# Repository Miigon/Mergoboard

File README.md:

# Mergoboard

38-key split ergonomic keyboard made with #ergogen.
## Note
This project is heavily based on [samoklava](https://github.com/soundmonster/samoklava) and uses much of the same footprints.
All the additional footprints or modified footprints are in the `footprints` folder.

## Screenshot
### rev0 (2022-05-02)

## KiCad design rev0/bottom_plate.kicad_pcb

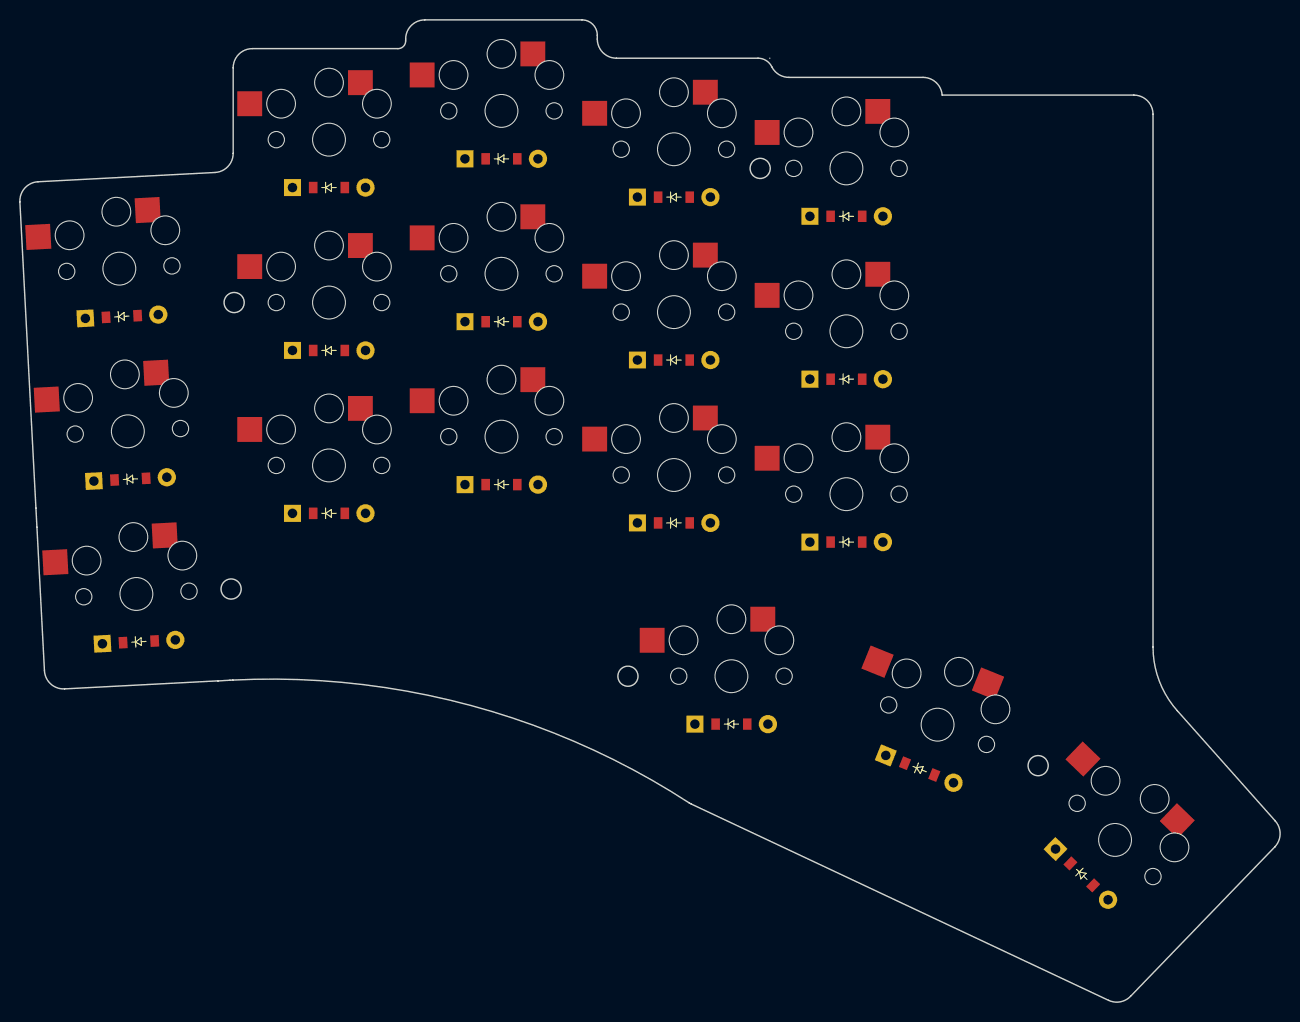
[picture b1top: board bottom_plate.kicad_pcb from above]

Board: 2 copper layers, 131.5 x 102.5 mm, 36 parts (0 on the bottom side), 27 nets, no tracks yet.

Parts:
D1, D2, D3, D4, D5, D6, D7, D8, D9, D10, D11, D12, D13, D14, D15, D16, D17, D18: ComboDiode
S1, S2, S3, S4, S5, S6, S7, S8, S9, S10, S11, S12, S13, S14, S15, S16, S17, S18: PG1350

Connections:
P4: D3.1, D3.2, D6.1, D6.2, D9.1, D9.2, D12.1, D12.2, D15.1, D15.2
P5: D2.1, D2.2, D5.1, D5.2, D8.1, D8.2, D11.1, D11.2, D14.1, D14.2
P6: D1.1, D1.2, D4.1, D4.2, D7.1, D7.2, D10.1, D10.2, D13.1, D13.2
P7: D16.1, D16.2, D17.1, D17.2, D18.1, D18.2
P14: S13.2, S14.2, S15.2, S18.2
P15: S10.2, S11.2, S12.2, S17.2
P18: S7.2, S8.2, S9.2, S16.2
P19: S4.2, S5.2, S6.2
P20: S1.2, S2.2, S3.2
far_thumb: D18.1, D18.2, S18.1
home_thumb: D17.1, D17.2, S17.1
index_bottom: D10.1, D10.2, S10.1
index_home: D11.1, D11.2, S11.1
index_top: D12.1, D12.2, S12.1
inner_bottom: D13.1, D13.2, S13.1
inner_home: D14.1, D14.2, S14.1
inner_top: D15.1, D15.2, S15.1
middle_bottom: D7.1, D7.2, S7.1
middle_home: D8.1, D8.2, S8.1
middle_top: D9.1, D9.2, S9.1
near_thumb: D16.1, D16.2, S16.1
pinky_bottom: D1.1, D1.2, S1.1
pinky_home: D2.1, D2.2, S2.1
pinky_top: D3.1, D3.2, S3.1
ring_bottom: D4.1, D4.2, S4.1
ring_home: D5.1, D5.2, S5.1
ring_top: D6.1, D6.2, S6.1

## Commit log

2022-05-03 rev0
2022-05-03 README, footprints and images
2022-05-06 rev1 start: fix TRRS connection (previously VCC on sleeve)
2023-07-21 README: fix date for rev0, add real-life shot
